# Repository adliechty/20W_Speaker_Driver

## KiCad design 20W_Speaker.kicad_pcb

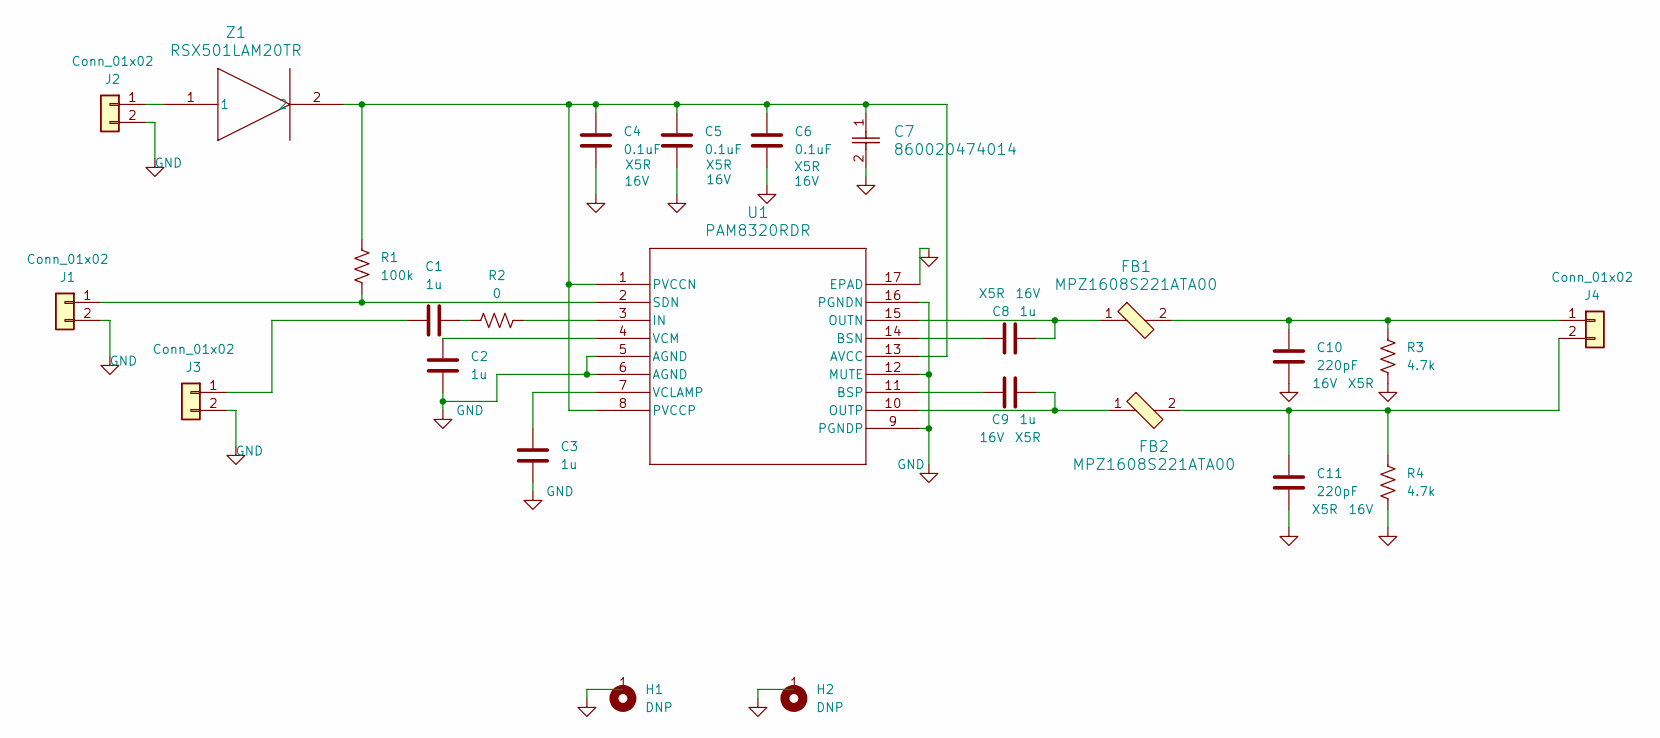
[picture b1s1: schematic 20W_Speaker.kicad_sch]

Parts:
C1, C2, C3, C8, C9: 1u; C_0603_1608Metric; Voltage 16V
C4, C5, C6: 0.1uF; C_0603_1608Metric; Voltage 16V
C7: 860020474014; CAP_WCAP-ATG5_8x11.5_WRE
C10, C11: 220pF; C_0603_1608Metric; Voltage 16V
FB1, FB2: MPZ1608S221ATA00; 0603; MPN MPZ1608S221ATA00; Digi-Key_PN 445-1565-1-ND
H1, H2: DNP; MountingHole_3.2mm_M3_DIN965_Pad
J1, J2, J3, J4: Conn_01x02; PinHeader_1x02_P2.54mm_VerticalFemale; Part Number 1-0201FBV0T
R1: 100k; R_0603_1608Metric
R2: 0; R_0603_1608Metric
R3, R4: 4.7k; R_0603_1608Metric
U1: PAM8320RDR; SO-16EP_3P9X9P9_DIO
Z1: RSX501LAM20TR; DIO_RB050LAM_ROM

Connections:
GND: C2.2, C3.2, C4.2, C5.2, C6.2, C7.2, C10.2, C11.2, H1.1, H2.1, J1.2, J2.2, J3.2, R3.2, R4.2, U1.5 (AGND), U1.6 (AGND), U1.9 (PGNDP), U1.12 (MUTE), U1.16 (PGNDN), U1.17 (EPAD)
unnamed: C1.2, R2.1
unnamed: J1.1, R1.2, U1.2 (SDN)
unnamed: J2.1, Z1.1
unnamed: C1.1, J3.1
unnamed: C10.1, FB1.2, J4.1, R3.1
unnamed: C11.1, FB2.2, J4.2, R4.1
unnamed: C4.1, C5.1, C6.1, C7.1, R1.1, U1.1 (PVCCN), U1.8 (PVCCP), U1.13 (AVCC), Z1.2
unnamed: C8.1, U1.14 (BSN)
unnamed: C9.1, U1.11 (BSP)
unnamed: R2.2, U1.3 (IN)
unnamed: C8.2, FB1.1, U1.15 (OUTN)
unnamed: C9.2, FB2.1, U1.10 (OUTP)
unnamed: C3.1, U1.7 (VCLAMP)
unnamed: C2.1, U1.4 (VCM)

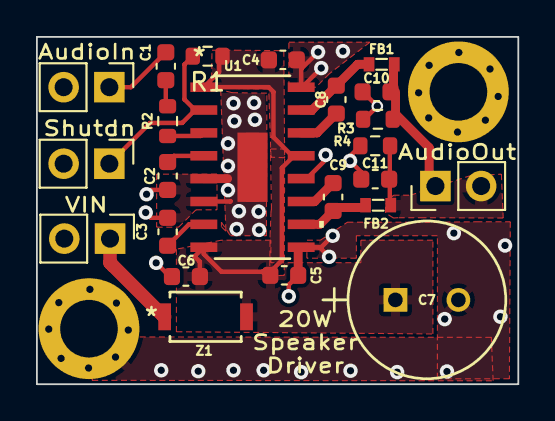
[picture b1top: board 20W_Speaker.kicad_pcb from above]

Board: 2 copper layers, 26.7 x 19.3 mm, 25 parts (0 on the bottom side), 15 nets.

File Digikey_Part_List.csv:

Digikey PN,Reference,Footprint,Value,Voltage,Type,Order Quantity,Total Price
13-CS0603KRX7R7BB105CT-ND,"C1, C2, C3, C8, C9",Capacitor_SMD:C_0603_1608Metric,1u,16V,X5R,5,0.45
490-10431-1-ND ,"C4, C5, C6",Capacitor_SMD:C_0603_1608Metric,0.1uF,16V,X5R,3,0.18
732-8831-1-ND,C7,470uF:CAP_WCAP-ATG5_8x11.5_WRE,860020474014,,,1,0.27
399-C0603C221K5RAC7867TR-ND,"C10, C11",Capacitor_SMD:C_0603_1608Metric,220pF,16V,X5R,2,0.01
445-MPZ1608S221ATA00TR-ND,"FB1, FB2",digikey-footprints:0603,MPZ1608S221ATA00,,,2,0.03
1212-1089-ND,"J1, J2, J3, J4",1x2FemaleVertical:PinHeader_1x02_P2.54mm_VerticalFemale,Conn_01x02,,,4,0.92
541-CRCW0603100KFKEBCCT-ND,R1,Resistor_SMD:R_0603_1608Metric,100k,,,1,0.02
541-2969-1-ND,R2,Resistor_SMD:R_0603_1608Metric,0,,,1,0.03
13-RC0603FR-7W4K7LCT-ND,"R3, R4",Resistor_SMD:R_0603_1608Metric,4.7k,,,2,0.04
PAM8320RDRDITR-ND,U1,PAM8320:SO-16EP_3P9X9P9_DIO,PAM8320RDR,,,1,0.71
RSX501LAM20TR-ND,Z1,5ADiode:DIO_RB050LAM_ROM,RSX501LAM20TR,,,1,0.11

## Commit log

2023-11-09 first add
2023-11-10 PCB submitted for order
